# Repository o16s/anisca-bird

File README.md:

# Anisca Bird

## Overview

Anisca Bird is a smart weighing and tracking device developed by Octanis Instruments in collaboration with the Swiss Ornithological Institute. The system replaces a bird's regular roosting place with a weighing and tracking device that can register a bird's identity and body weight throughout the year without causing stress to the animal.

This repository contains the firmware, PCB design files, and mechanical designs to build and operate the Anisca Bird system.

## Key Features

- **RFID Identification**: Automatically reads passive RFID tags attached to birds
- **Weight Measurement**: Precision load cell with 1g resolution when calibrated
- **Data Storage**: Onboard memory for up to 18 years of weight records
- **Wireless Connectivity**: Optional Sigfox connectivity for remote data transmission
- **USB Connection**: Easy data transfer via USB-C port
- **Long Battery Life**: Up to 1 year with the external battery box
- **Modular Design**: Easy to modify, repair, or upgrade

## Repository Structure

- **`/mechanical`**: Mechanical design files (STEP format)
- **`/nestbox-electronics-master`**: PCB design files for the main board, RFID antenna, and battery box
  - **`/LF_Antenna_v3`**: RFID antenna PCB design
  - **`/Nestbox_v3_3*`**: Main board iterations
  - **`/battery_box`**: Battery box PCB design
  - **`/lib_fp.pretty`**: KiCad footprint libraries
  - **`/lib_sch`**: KiCad schematic libraries
- **`/nestbox-firmware-REV3.3`**: Firmware source code
  - **`/nestbox-fw`**: Core firmware files
  - **`/Core`**: Main application code
  - **`/Drivers`**: Hardware driver files
  - **`/Middlewares`**: Middleware components
  - **`/USB_DEVICE`**: USB communication stack

## Hardware Overview

The Anisca Bird system consists of three main components:

1. **Reader**: Contains the main PCB with microcontroller, load cell interface, RFID reader, flash memory, and connectivity options. Housed in a water-resistant aluminum case.

2. **Perch**: Varnished plywood perch with integrated 125kHz RFID antenna for tag reading with up to 10cm range.

3. **Battery Box**: External battery case with four 10Ah NiMH D-cells providing up to 1 year of operation.

## Firmware Overview

The firmware is built for STM32L433 microcontroller and provides the following functionality:

- RFID tag detection and decoding
- Weight measurement and analysis
- Low-power operation for extended battery life
- USB communication for data retrieval and configuration
- Optional Sigfox connectivity for remote data transmission

## License

Where not otherwise specified, the [GPL License](LICENSE) applies.

## Contact

For commercial support or to request an Anisca Bird system, please contact:

Octanis Instruments GmbH  
Europa-Strasse 33, 8152 Glattbrugg, Switzerland  
info@octanis.ch  
www.octanis.ch

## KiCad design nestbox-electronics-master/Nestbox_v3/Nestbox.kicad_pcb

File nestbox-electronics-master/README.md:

# Nestbox Electronics

All electronics design files and documentations are stored here.

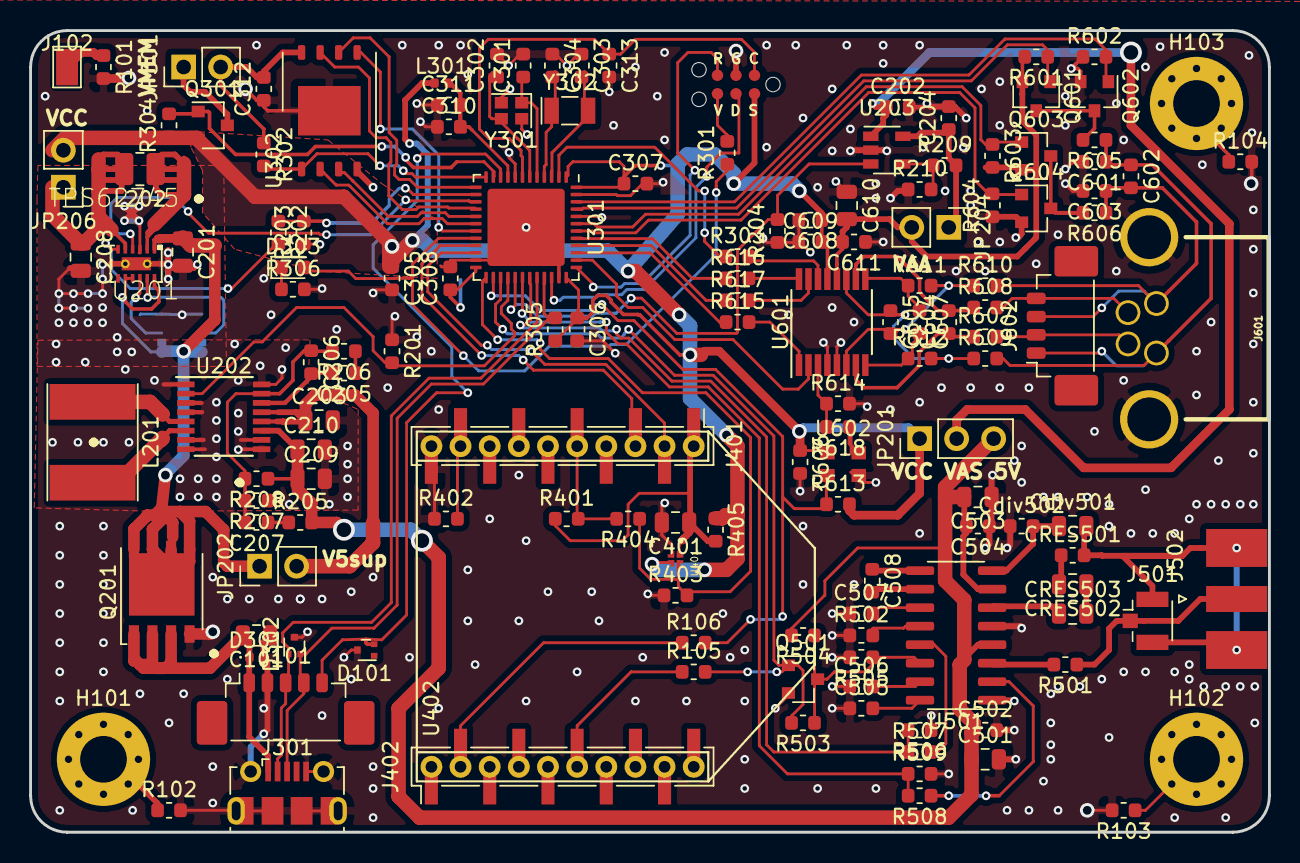
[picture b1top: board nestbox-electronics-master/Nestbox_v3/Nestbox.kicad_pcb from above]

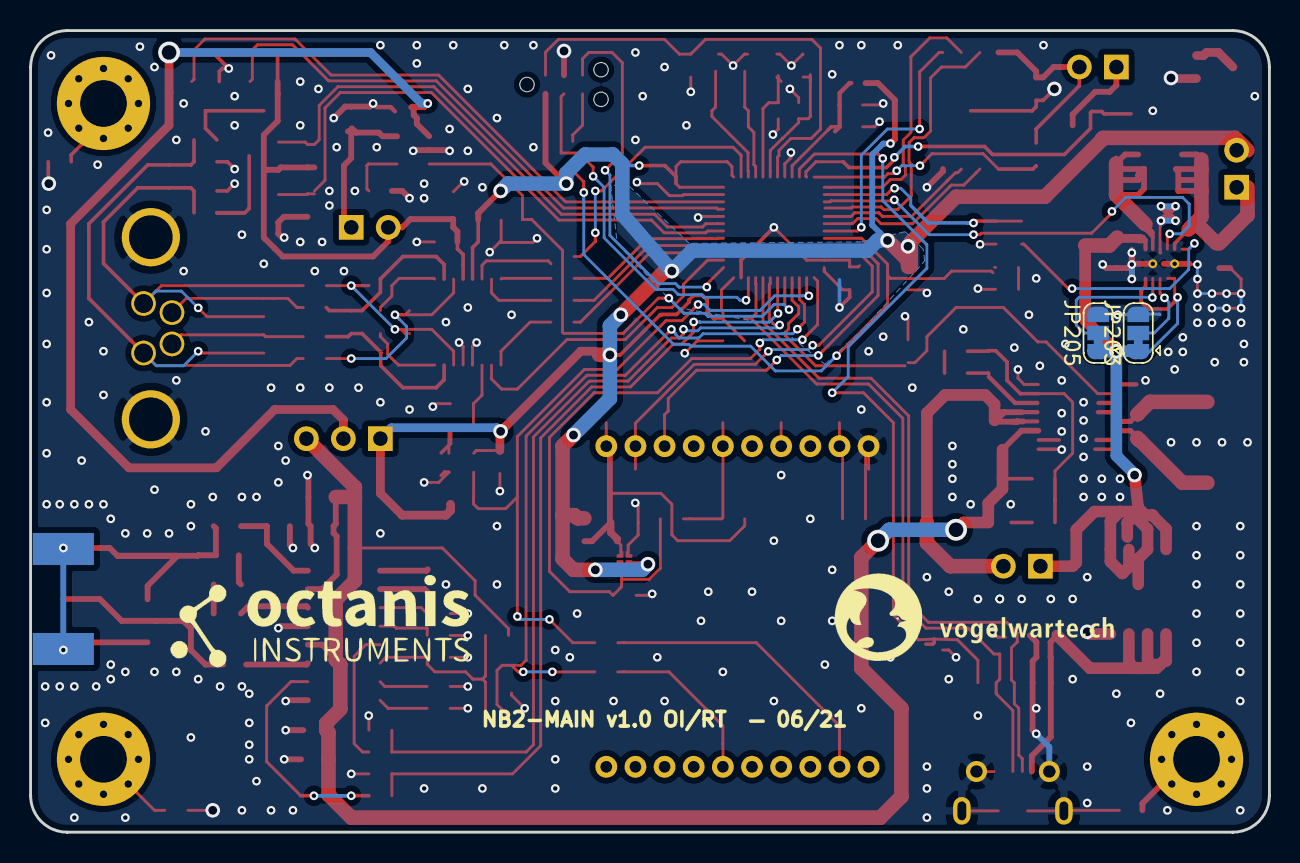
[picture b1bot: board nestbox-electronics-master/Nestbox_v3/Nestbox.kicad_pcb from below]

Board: 2 copper layers, 85.0 x 55.0 mm, 150 parts (4 on the bottom side), 108 nets.

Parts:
C101, C201, C203, C208, C209, C210, C401, C501, C503, C610: 10u; C_0805_2012Metric
C202, C311, C312, C608: 1u; C_0603_1608Metric
C204: 1u or 4u7 for adjustable version; C_0603_1608Metric
C205: 330p; C_0603_1608Metric
C206: 10p; C_0603_1608Metric
C207: 33p; C_0603_1608Metric
C301, C302: 12p; C_0603_1608Metric
C303, C304: 22p; C_0603_1608Metric
C305: 4u7; C_0603_1608Metric
C306, C307, C308, C313, C502, C504, C507, C606, C609: 100n; C_0603_1608Metric
C310, C505, C506, C611: 10n; C_0603_1608Metric
C508: DNP or 100n; C_0603_1608Metric
C601, C603, C604: 100n 1% DNP; C_0603_1608Metric
C602: 1u DNP; C_0603_1608Metric
C605, C607: 100n DNP; C_0603_1608Metric
CRES501: 0R; C_0603_1608Metric
CRES502, CRES503: 1n5 450V C0G; C_0805_2012Metric
Cdiv501: 10p 500V; C_0805_2012Metric
Cdiv502: 1n; C_0603_1608Metric
D101, D302: ESD7205; SOT-723
D301: TVS DIODE 12V 23.7V; D_0402_1005Metric
D303: LED_YELLOW; LED_0603_1608Metric
G101: LOGO; oi_logo_small
H101, H102, H103: MountingHole_Pad; MountingHole_3.2mm_M3_Pad_Via
J101: FC-M8-5; Molex_PicoBlade_53398-0571_1x05-1MP_P1.25mm_Vertical
J102: Chassis Pin; SMD_PAD
J301: USB_B_Micro; USB_Micro-B_Molex-105017-0001
J401, J402: Conn_01x10_Female; PinSocket_1x10_P2.00mm_Vertical_SMD_Pin1Left
J501: Conn_RFID_UFL_ALT; U.FL_Hirose_U.FL-R-SMT-1_Vertical
J502: Conn_RFID_SMA; SMA_Molex_EdgeMount
J601: LOAD_CELL_CONN_01X04; MB08MBSAFF04RA
J602: LOAD_CELL_CONN_01X04; Molex_PicoBlade_53398-0471_1x04-1MP_P1.25mm_Vertical
JP201: Jumper_3_Bridged12; PinHeader_1x03_P2.54mm_Vertical
JP202: 5V boost supply jumper; PinHeader_1x02_P2.54mm_Vertical
JP203: vsel 0.2; SolderJumper-3_P1.3mm_Bridged12_RoundedPad1.0x1.5mm
JP204: VAA jumper; PinHeader_1x02_P2.54mm_Vertical
JP205: vsel 0.1; SolderJumper-3_P1.3mm_Bridged12_RoundedPad1.0x1.5mm
JP206, JP301: Jumper_NC_Small; PinHeader_1x02_P2.54mm_Vertical
L201: 5uH; L_Taiyo-Yuden_NR-60xx_HandSoldering
L202: 4.7uH; L_1008_2520Metric
L301: 10u; L_0402_1005Metric
LOGO101: Logo_Open_Hardware_Small; VogelwarteLogo3
P301: TC2030-MCP; TC2030-MCP-NL
Q201: TPH1R712MDL1Q; TDSON-8-1_HandSoldering
Q301, Q601, Q603: DMG2301L-7; SOT-23
Q501, Q602, Q604: NMOS 30V 4A; SOT-23
R101, R102, R103, R104, R205, R401, R403: 10k; R_0603_1608Metric
R105, R106, R204, R209, R210, R301, R402, R404, R405, R503, R505, R506, R509, R613, R614: DNP; R_0603_1608Metric
R201, R202, R302, R304, R504, R601, R602, R603, R604: 82k; R_0603_1608Metric
R203: 47k; R_0603_1608Metric
R206: 15k; R_0603_1608Metric
R207: 162k 1%; R_0603_1608Metric
R208: 649k 1%; R_0603_1608Metric
R303: 100R; R_0603_1608Metric
R305: 1k5; R_0603_1608Metric
R306: 1k; R_0603_1608Metric
R501, R502, R507, R508, R605, R606, R607, R608, R609, R610, R611, R612, R618: 0R; R_0603_1608Metric
R615, R616, R617: 47R; R_0603_1608Metric
U201: TPS62745; WSON_3x2mm_12pin
U202: LTC3534; SSOP-16_3.9x4.9mm_P0.635mm
U203: 3.0V LDO; SOT-23-5
U301: STM32L433CCxx; QFN-48-1EP_7x7mm_P0.5mm_EP5.3x5.3mm
U302: 1Gb NAND Flash; 8-LGA-6x8mm
U401: Power Switch 2A, 800us soft start; IC_MIC94085YFT-TR
U402: XBEE
U501: EM4095; SOIC-16_3.9x9.9mm_P1.27mm
U601: ADS1220; TSSOP-16_4.4x5mm_P0.65mm
U602: SIT1602BI 4.096 MHz; Oscillator_SMD_EuroQuartz_XO32-4Pin_3.2x2.5mm
Y301: 16MHz 10ppm 9pF; Crystal_SMD_2016-4Pin_2.0x1.6mm
Y302: 32kHz 20ppm 12.5pF; Crystal_SMD_MicroCrystal_CC7V-T1A-2Pin_3.2x1.5mm

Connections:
+5V: C209.1, C210.1, C501.1, C502.1, C503.2, C504.2, JP201.3, R205.2, R208.1, R504.2, U202.11, U501.4, U501.7
+BATT: C201.1, JP202.1, JP203.1, JP205.1, Q201.3, U201.1, U201.8, U201.9, U201.12
/ADC_CLK_EN: R106.2, R613.1, U301.26, U602.1
/Communication/RF_CTS: J402.2, R106.1, U402.12
/Communication/RF_ENABLE: R403.2, R404.1, U301.25, U401.4
/Communication/RF_RTS: J402.6, R105.1, U402.16
/Communication/RF_RX: J401.3, U301.21, U402.3
/Communication/RF_TX: J401.2, U301.22, U402.2
/Communication/SUPER_B_EN: J401.5, R401.2, R404.2, U402.5
/Communication/SUPER_B_IO0: J401.7, U402.7
/Communication/dtr: J401.9, R402.2, U402.9
/Control/5V_ENABLE: R201.2, U202.2, U301.28
/Control/BAT_TEST_ENABLE: U201.4, U301.15
/Control/DBG_LED1: D303.2, R301.1, U301.20
/Control/FLASH_POWER_ON_N: Q301.1, R304.2, U301.11
/Control/HK_BAT_V: R202.1, R203.2, U301.14
/Control/LOADCELL_SPI_CS: U301.38, U601.2
/Control/QSPI_CSN: R302.2, U301.12, U302.1
/Control/QSPI_IO0: U301.19, U302.5
/Control/QSPI_IO1: U301.18, U302.2
/Control/QSPI_IO2: U301.17, U302.3
/Control/QSPI_IO3: U301.16, U302.7
/Control/QSPI_SCK: U301.13, U302.6
/Control/RFID_CLK: R506.2, R507.1, U301.31
/Control/RFID_DATA: R508.2, R509.1, U301.30
/Control/SPI_CLK: R615.1, U301.39
/Control/SPI_MISO: R617.1, U301.40
/Control/SPI_MOSI: R616.1, U301.41
/Load_Cell/ADC_CLK: R614.1, R618.2, U601.3
/Load_Cell/AIN1: C604.2, R608.1, U601.10
/Load_Cell/AIN2: C604.1, R607.1, U601.7
/Load_Cell/DRDY_N: R303.2, U601.14
/Load_Cell/EXC_A: C601.1, C602.1, J601.1, J602.1, R605.1, R609.2
/Load_Cell/EXC_A_N: Q602.1, R602.2, U301.46
/Load_Cell/EXC_A_P: Q601.1, R601.1, U301.45
/Load_Cell/EXC_B: C602.2, C603.1, J601.3, J602.3, R606.1, R610.2
/Load_Cell/EXC_B_N: Q604.1, R604.2, U301.42
/Load_Cell/EXC_B_P: Q603.1, R603.1, U301.43
/Load_Cell/green: J601.2, J602.2, R607.2
/Load_Cell/white: J601.4, J602.4, R608.2
/RFID/ant1: J501.1, J502.1, R501.1
/RFID/ant2: CRES501.2, Cdiv501.2, J501.2, J502.2
/RFID/demod_out: R507.2, U501.13
/RFID/rdyclk: R508.1, U501.2
/RFID/shd: Q501.3, R503.1, R504.1, R505.1, U501.14
/RFID_SLEEP_N: Q501.1, R105.2, R503.2, U301.27
/VAA_LDO_EN: R204.2, U203.3, U301.29
BAT_IN: C101.2, D301.1, J101.1, J301.1, Q201.1
GND: C101.1, C201.2, C202.2, C203.2, C204.2, C208.2, C209.2, C210.2, C301.2, C302.2, C303.1, C304.1, C305.2, C306.2, C307.2, C308.2, C310.1, C311.1, C312.1, C313.2, C401.2, C501.2, C502.2, C503.1, C504.1, C505.1, C506.1, C507.1, C601.2, C603.2, C606.2, C608.2, C609.1, C610.1, C611.1, Cdiv502.1, D101.3, D301.2, D302.3, J101.2, J301.5, J301.6, J401.10, J601.SH, JP203.3, JP205.3, P301.3, Q201.2, Q501.2, Q602.2, Q604.2, R101.2, R102.2, R103.2, R104.2, R201.1, R203.1, R204.1, R207.1, R210.1, R306.2, R402.1, R403.1, R502.1, R505.2, R506.1, R509.2, R602.1, R604.1, R614.2, U201.3, U201.GND1, U201.GND2, U202.1, U202.3, U202.4, U202.7, U202.8, U202.9, U202.10, U202.16, U203.2, U301.8, U301.23, U301.35, U301.44, U301.47, U301.49, U302.4, U302.9, U401.2, U402.10, U501.1, U501.5, U601.4, U601.5, U602.2, Y301.2, Y301.4
NRST: C313.1, P301.1, U301.7
unnamed: C202.1, JP201.2, U203.1
unnamed: C203.1, JP202.2, U202.12, U202.13
unnamed: C204.1, JP204.1, R209.2, U203.5
unnamed: C205.1, R206.1
unnamed: C205.2, C206.2, U202.14
unnamed: C206.1, C207.2, R206.2, R207.2, R208.2, U202.15
unnamed: C207.1, R205.1
unnamed: C208.1, JP206.1, L202.2, U201.5
unnamed: C301.1, U301.5, Y301.1
unnamed: C302.1, U301.6, Y301.3
unnamed: C303.2, U301.3, Y302.2
unnamed: C304.2, U301.4, Y302.1
unnamed: C310.2, C311.2, L301.2, U301.9
unnamed: C312.2, JP301.2, R302.1, U302.8
unnamed: C505.2, U501.16
unnamed: C506.2, U501.15
unnamed: C507.2, U501.11
unnamed: C508.1, U501.9
unnamed: C508.2, U501.10
unnamed: C605.1, R609.1, R612.2, U601.11
unnamed: C605.2, R610.1, R611.2, U601.6
unnamed: C607.1, R611.1, U601.9
unnamed: C607.2, R612.1, U601.8
unnamed: CRES501.1, CRES502.2
unnamed: CRES502.1, CRES503.2
unnamed: CRES503.1, U501.6
unnamed: Cdiv501.1, Cdiv502.2, U501.8
unnamed: D303.1, R306.1
unnamed: H101.1, R102.1
unnamed: H102.1, R103.1
unnamed: H103.1, R104.1
unnamed: J102.1, R101.1
unnamed: JP203.2, U201.10
unnamed: JP205.2, U201.11
unnamed: JP301.1, Q301.3
unnamed: L201.1, U202.5
unnamed: L201.2, U202.6
unnamed: L202.1, U201.2
unnamed: Q601.3, Q602.3, R605.2
unnamed: Q603.3, Q604.3, R606.2
unnamed: R202.2, U201.6
unnamed: R209.1, R210.2, U203.4
unnamed: R303.1, U301.2
unnamed: R501.2, U501.3
unnamed: R502.2, U501.12
unnamed: R615.2, U601.1
unnamed: R616.2, U601.16
unnamed: R617.2, U601.15
unnamed: R618.1, U602.3
RTC_OUT_CALIB: P301.6, R301.2
SWCLK: P301.5, U301.37
SWDIO: P301.4, U301.34
USB_D+: D302.2, J101.4, J301.3, R305.2, U301.33
USB_D-: D302.1, J101.3, J301.2, U301.32
USER_GPIO: D101.2, J101.5, U301.10
VAA: C610.2, C611.2, JP204.2, Q601.2, Q603.2, R601.2, R603.2, U601.12
VCC: C305.1, C306.1, C307.1, C308.1, C606.1, C608.1, C609.2, JP201.1, JP206.2, L301.1, P301.2, Q301.2, R304.1, R305.1, R405.1, R613.2, U301.1, U301.24, U301.36, U301.48, U401.3, U601.13, U602.4
VCOM: C401.1, J401.1, R401.1, R405.2, U401.1, U402.1

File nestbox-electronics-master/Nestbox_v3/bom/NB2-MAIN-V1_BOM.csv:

Reference, Quantity, Value, Footprint, Datasheet, MPN, MPN-adj, MPN2, Description, Height
C101 C201 C203 C208 C209 C210 C401 C501 C503 C610 ,10,"10u","Capacitor_SMD:C_0805_2012Metric",""
C202 C311 C312 C608 ,4,"1u","Capacitor_SMD:C_0603_1608Metric",""
C204 ,1,"1u or 4u7 for adjustable version","Capacitor_SMD:C_0603_1608Metric",""
C205 ,1,"330p","Capacitor_SMD:C_0603_1608Metric",""
C206 ,1,"10p","Capacitor_SMD:C_0603_1608Metric",""
C207 ,1,"33p","Capacitor_SMD:C_0603_1608Metric",""
C301 C302 ,2,"12p","Capacitor_SMD:C_0603_1608Metric","~"
C303 C304 ,2,"22p","Capacitor_SMD:C_0603_1608Metric","~"
C305 ,1,"4u7","Capacitor_SMD:C_0603_1608Metric","~"
C306 C307 C308 C313 C502 C504 C507 C606 C609 ,9,"100n","Capacitor_SMD:C_0603_1608Metric","~"
C310 C505 C506 C611 ,4,"10n","Capacitor_SMD:C_0603_1608Metric","~"
C508 ,1,"DNP or 100n","Capacitor_SMD:C_0603_1608Metric","DNP"
C602 ,1,"1u DNP","Capacitor_SMD:C_0603_1608Metric",""
C601 C603 C604 ,3,"100n 1% DNP","Capacitor_SMD:C_0603_1608Metric",""
C605 C607 ,2,"100n DNP","Capacitor_SMD:C_0603_1608Metric",""
CRES501 ,1,"0R","Capacitor_SMD:C_0603_1608Metric",""
CRES502 CRES503 ,2,"1n5 450V C0G","Capacitor_SMD:C_0805_2012Metric","","CGA4F4C0G2W152J085AE","","","",""
Cdiv501 ,1,"10p 500V","Capacitor_SMD:C_0805_2012Metric","","C0805C100JDGACTU","","","",""
Cdiv502 ,1,"1n","Capacitor_SMD:C_0603_1608Metric",""
D101 D302 ,2,"ESD7205","Package_TO_SOT_SMD:SOT-723","","SZESD7205DT5G","","","",""
D301 ,1,"TVS DIODE 12V 23.7V","Diode_SMD:D_0402_1005Metric","~","ESD9X12ST5G","","","",""
D303 ,1,"LED_YELLOW","LED_SMD:LED_0603_1608Metric",""
G101 ,1,"LOGO","lib-fp-global:oi_logo_small",""
H101 H102 H103 ,3,"MountingHole_Pad","MountingHole:MountingHole_3.2mm_M3_Pad_Via","~"
J101 ,1,"FC-M8-5","Connector_Molex:Molex_PicoBlade_53398-0571_1x05-1MP_P1.25mm_Vertical","http://www.mouser.com/ds/2/18/40_c091_abd_e-75918.pdf","53398-0571","","","",""
J102 ,1,"Chassis Pin","lib_fp:SMD_PAD","~"
J301 ,1,"USB_B_Micro","Connector_USB:USB_Micro-B_Molex-105017-0001","~"
J401 J402 ,2,"Conn_01x10_Female","Connector_PinSocket_2.00mm:PinSocket_1x10_P2.00mm_Vertical_SMD_Pin1Left","~","1-2307813-0","","","",""
J501 ,1,"Conn_RFID_UFL_ALT","Connector_Coaxial:U.FL_Hirose_U.FL-R-SMT-1_Vertical"," ~","U.FL-R-SMT(10)","","","",""
J502 ,1,"Conn_RFID_SMA","lib_fp:SMA_Molex_EdgeMount"," ~","0732512120","","","",""
J601 ,1,"LOAD_CELL_CONN_01X04","lib_fp:MB08MBSAFF04RA","","M8S-04PMMR-SF8001","","MB08MBSAFF04RA","",""
J602 ,1,"LOAD_CELL_CONN_01X04","Connector_Molex:Molex_PicoBlade_53398-0471_1x04-1MP_P1.25mm_Vertical","","53398-0471","","","",""
JP201 ,1,"Jumper_3_Bridged12","Connector_PinHeader_2.54mm:PinHeader_1x03_P2.54mm_Vertical","~"
JP202 ,1,"5V boost supply jumper","Connector_PinHeader_2.54mm:PinHeader_1x02_P2.54mm_Vertical","~"
JP203 ,1,"vsel 0.2","Jumper:SolderJumper-3_P1.3mm_Bridged12_RoundedPad1.0x1.5mm","~"
JP204 ,1,"VAA jumper","Connector_PinHeader_2.54mm:PinHeader_1x02_P2.54mm_Vertical","~"
JP205 ,1,"vsel 0.1","Jumper:SolderJumper-3_P1.3mm_Bridged12_RoundedPad1.0x1.5mm","~"
JP206 JP301 ,2,"Jumper_NC_Small","Connector_PinHeader_2.54mm:PinHeader_1x02_P2.54mm_Vertical","~"
L201 ,1,"5uH","Inductor_SMD:L_Taiyo-Yuden_NR-60xx_HandSoldering","","MSS7341-502NLD","","","",""
L202 ,1,"4.7uH","Inductor_SMD:L_1008_2520Metric","","DFE252010P-4R7M=P2","","","",""
L301 ,1,"10u","Inductor_SMD:L_0402_1005Metric","~","MPZ1005S300CT000","","","",""
LOGO101 ,1,"Logo_Open_Hardware_Small","lib_fp:VogelwarteLogo3","~"
P301 ,1,"TC2030-MCP","lib-fp-global:TC2030-MCP-NL",""
Q201 ,1,"TPH1R712MDL1Q","lib_fp:TDSON-8-1_HandSoldering","","TPH1R712MD,L1Q","","","",""
Q301 Q601 Q603 ,3,"DMG2301L-7","Package_TO_SOT_SMD:SOT-23","","DMG2301L-7","","","",""
Q501 Q602 Q604 ,3,"NMOS 30V 4A","Package_TO_SOT_SMD:SOT-23","","SI2316DS-T1-E3","","","",""
R101 R102 R103 R104 R205 R401 R403 ,7,"10k","Resistor_SMD:R_0603_1608Metric","~"
R105 R106 R204 R209 R210 R301 R402 R404 R405 R503 R505 R506 R509 R613 R614 ,15,"DNP","Resistor_SMD:R_0603_1608Metric","~"
R201 R202 R302 R304 R504 R601 R602 R603 R604 ,9,"82k","Resistor_SMD:R_0603_1608Metric",""
R203 ,1,"47k","Resistor_SMD:R_0603_1608Metric",""
R206 ,1,"15k","Resistor_SMD:R_0603_1608Metric",""
R207 ,1,"162k 1%","Resistor_SMD:R_0603_1608Metric","","RC0402FR-07162KL","","","",""
R208 ,1,"649k 1%","Resistor_SMD:R_0603_1608Metric","","RC0402FR-07649KL","","","",""
R303 ,1,"100R","Resistor_SMD:R_0603_1608Metric","~"
R305 ,1,"1k5","Resistor_SMD:R_0603_1608Metric","~"
R306 ,1,"1k","Resistor_SMD:R_0603_1608Metric",""
R501 R502 R507 R508 R605 R606 R607 R608 R609 R610 R611 R612 R618 ,13,"0R","Resistor_SMD:R_0603_1608Metric",""
R615 R616 R617 ,3,"47R","Resistor_SMD:R_0603_1608Metric",""
U201 ,1,"TPS62745","lib_fp:WSON_3x2mm_12pin","","TPS62745DSSR","","","",""
U202 ,1,"LTC3534","Package_SO:SSOP-16_3.9x4.9mm_P0.635mm","","LTC3534EDHC#PBF","","","",""
U203 ,1,"3.0V LDO ","Package_TO_SOT_SMD:SOT-23-5","","TPS70630DBVR","TPS76201QDBVRQ1 ","TPS7A20","",""
U301 ,1,"STM32L433CCxx","Package_DFN_QFN:QFN-48-1EP_7x7mm_P0.5mm_EP5.3x5.3mm","http://www.st.com/st-web-ui/static/active/en/resource/techni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","STM32L433CCU6","","","",""
U302 ,1,"1Gb NAND Flash","lib_fp:8-LGA-6x8mm","","GD5F1GQ4UFYIGR","","","",""
U401 ,1,"Power Switch 2A, 800us soft start","lib_fp:IC_MIC94085YFT-TR","","MIC94082YFT-TR","","","",""
U402 ,1,"XBEE","lib_fp:XBEE","","SuperBx","","","",""
U501 ,1,"EM4095","Package_SO:SOIC-16_3.9x9.9mm_P1.27mm","","EM4095","","","",""
U601 ,1,"ADS1220","Package_SO:TSSOP-16_4.4x5mm_P0.65mm","","ADS1220IPW","","","",""
U602 ,1,"SIT1602BI 4.096 MHz","Oscillator:Oscillator_SMD_EuroQuartz_XO32-4Pin_3.2x2.5mm","https://abracon.com/Oscillators/ASDMB.pdf","SIT1602BI-21-XXE-4.096000","","","",""
Y301 ,1,"16MHz 10ppm 9pF","lib_fp:Crystal_SMD_2016-4Pin_2.0x1.6mm","","ECS-160-9-37-CKM-TR","",""," 16MHz ±10ppm Crystal 9pF 100 Ohms 4-SMD, No Lead ","0.6"
Y302 ,1,"32kHz 20ppm 12.5pF","lib_fp:Crystal_SMD_MicroCrystal_CC7V-T1A-2Pin_3.2x1.5mm","~","CM7V-T1A-32.768kHz-12.5pF-20PPM-TB-QC","","","",""

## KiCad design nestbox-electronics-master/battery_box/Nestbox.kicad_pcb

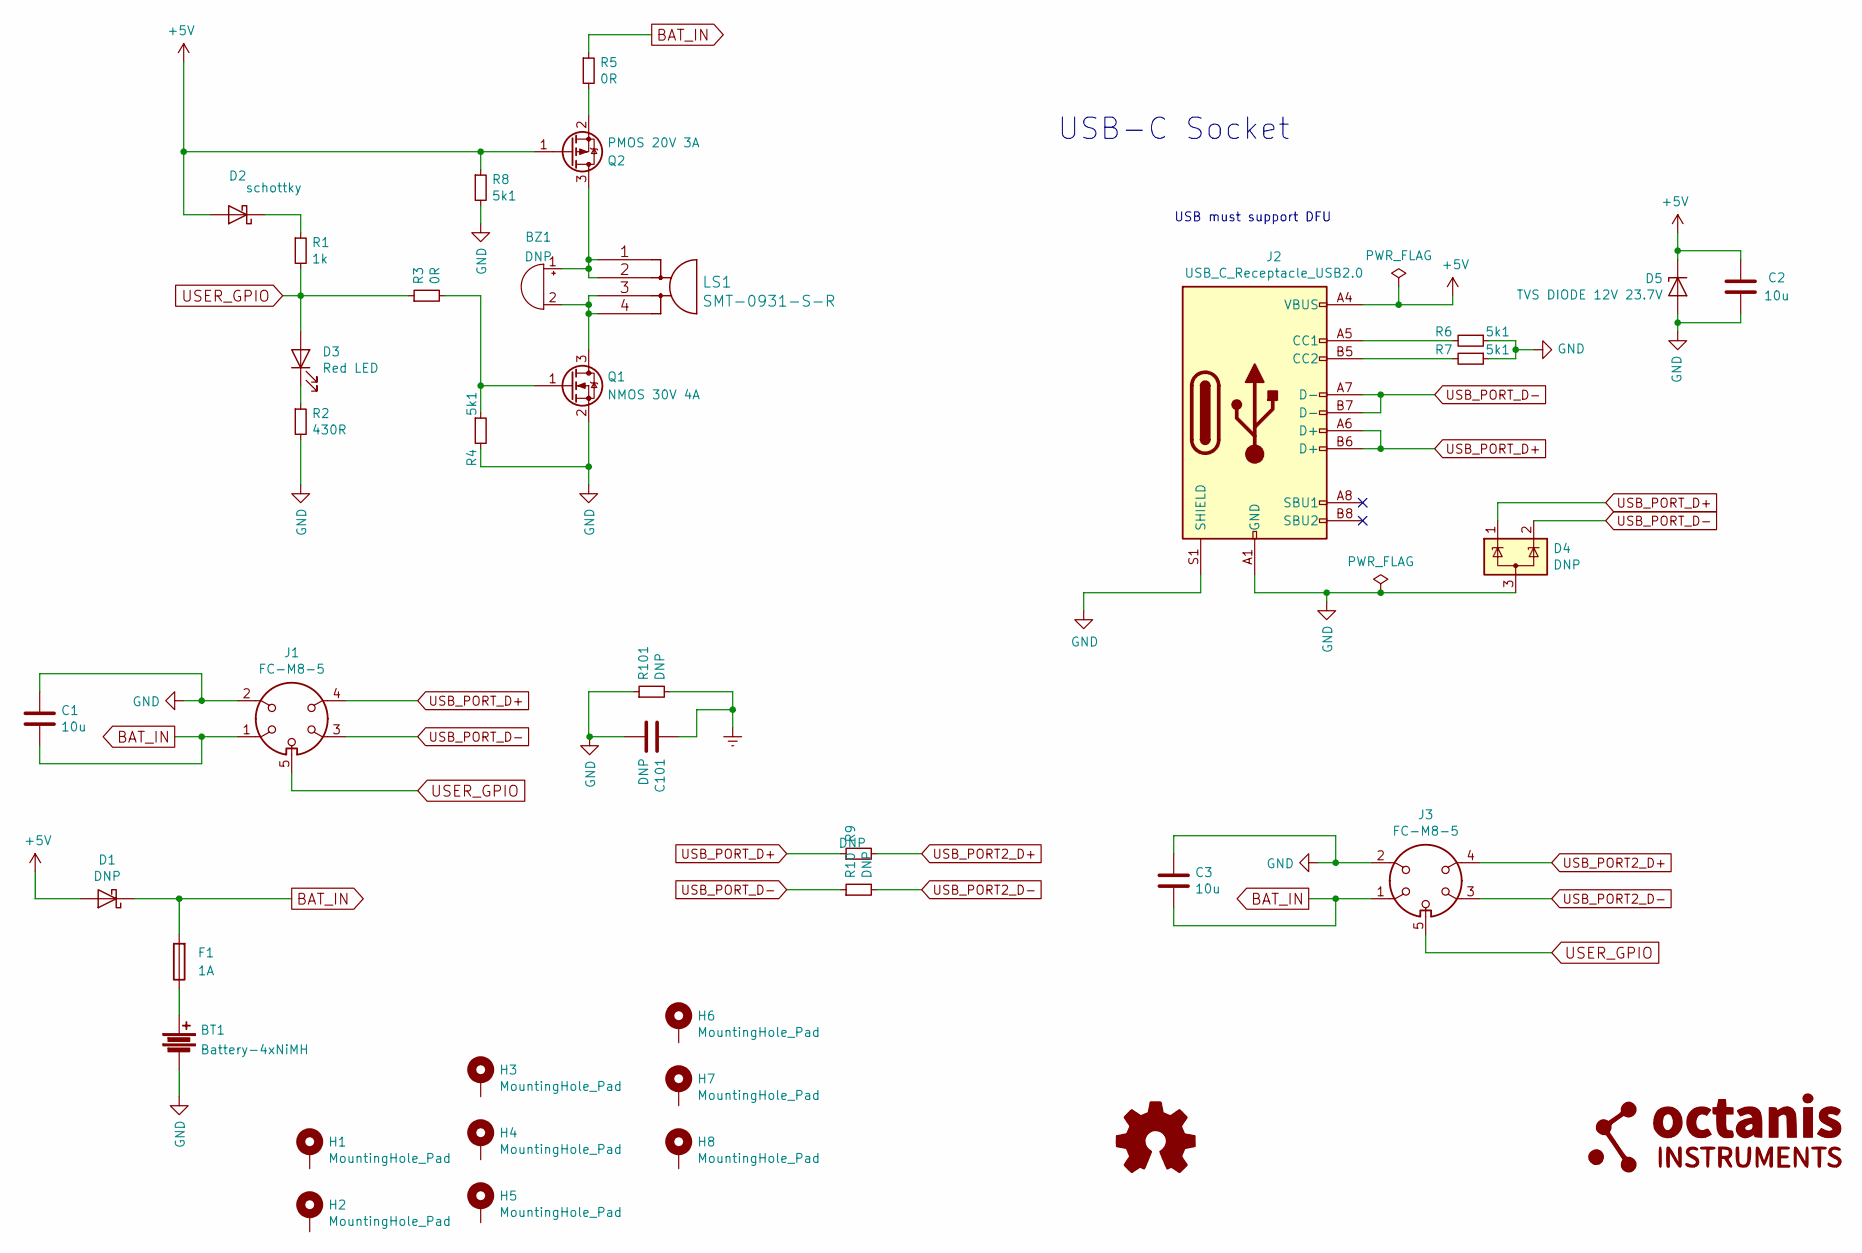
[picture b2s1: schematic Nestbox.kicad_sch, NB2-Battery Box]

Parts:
BT1: Battery-4xNiMH; TerminalBlock_Dinkle_DT-55-B01X-02_P10.00mm
BZ1: DNP; Buzzer_CUI_CPT-9019S-SMT; MPN SMT-0827-SW-5V-R
C1, C2, C3: 10u; C_0805_2012Metric
C101: DNP; C_0805_2012Metric
D1: DNP; D_SOD-323; MPN B0520WS-7-F
D2: schottky; D_SOD-323; MPN B0520WS-7-F
D3: Red LED; LED_D5.0mm; MPN WP934EW/ID
D4: DNP; SOT-723; MPN SZESD7205DT5G
D5: TVS DIODE 12V 23.7V; D_SOD-523; MPN UCLAMP1201H.TCT
F1: 1A; 0154001.DR; MPN 0154001.DR
G1: LOGO; oi_logo_small
H1, H3, H5, H7: MountingHole_Pad; MountingHole_4.5mm
H2, H4, H6, H8: MountingHole_Pad; MountingHole_3.5mm
J1, J3: FC-M8-5; M8-5pin_2.9mm_hole; MPN2 1424240
J2: USB_C_Receptacle_USB2.0; USB_C_Receptacle_HRO_TYPE-C-31-M-12; MPN USB4105-GF-A
LOGO1: Logo_Open_Hardware_Small; VogelwarteLogo3
LS1: SMT-0931-S-R; MPN SMT-0931-S-R
Q1: NMOS 30V 4A; SOT-23; MPN PMV45EN2R
Q2: PMOS 20V 3A; SOT-23; MPN DMP2160U-7
R1: 1k; R_0603_1608Metric
R2: 430R; R_0603_1608Metric
R3, R5: 0R; R_0603_1608Metric
R4, R6, R7, R8: 5k1; R_0603_1608Metric
R9, R10, R101: DNP; R_0603_1608Metric

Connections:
+5V: C2.1, D1.2 (A), D2.2 (A), D5.1 (K), J2.A4 (VBUS), J2.A9 (VBUS), J2.B4 (VBUS), J2.B9 (VBUS), Q2.1 (G), R8.1
BAT_IN: C1.2, C3.2, D1.1 (K), F1.2, J1.1, J3.1, R5.1
Earth: C101.1, R101.2
GND: BT1.2, C1.1, C2.2, C3.1, C101.2, D4.3 (A), D5.2 (A), J1.2, J2.A1 (GND), J2.A12 (GND), J2.B1 (GND), J2.B12 (GND), J2.S1 (SHIELD), J3.2, Q1.2 (S), R2.2, R4.2, R6.1, R7.1, R8.2, R101.1
unnamed: BT1.1, F1.1
unnamed: BZ1.1 (-), LS1.1, LS1.2, Q2.3 (D)
unnamed: BZ1.2 (+), LS1.3, LS1.4, Q1.3 (D)
unnamed: D2.1 (K), R1.1
unnamed: D3.1 (K), R2.1
unnamed: J2.A5 (CC1), R6.2
unnamed: J2.B5 (CC2), R7.2
unnamed: Q1.1 (G), R3.2, R4.1
unnamed: Q2.2 (S), R5.2
USB_PORT2_D+: J3.4, R9.2
USB_PORT2_D-: J3.3, R10.2
USB_PORT_D+: D4.1 (K), J1.4, J2.A6 (D+), J2.B6 (D+), R9.1
USB_PORT_D-: D4.2 (K), J1.3, J2.A7 (D-), J2.B7 (D-), R10.1
USER_GPIO: D3.2 (A), J1.5, J3.5, R1.2, R3.1

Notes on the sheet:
USB-C Socket
USB must support DFU

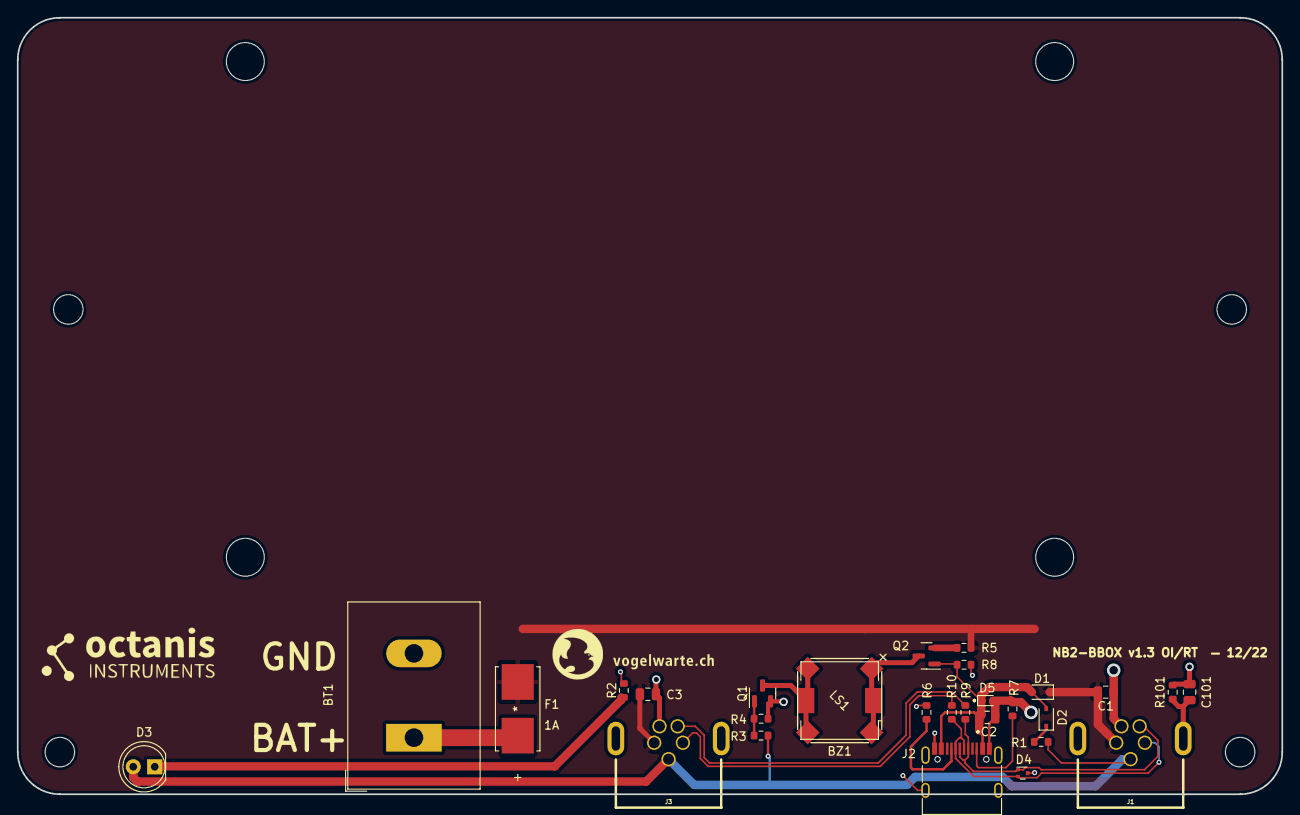
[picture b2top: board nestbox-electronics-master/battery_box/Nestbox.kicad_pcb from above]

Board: 2 copper layers, 150.0 x 92.1 mm, 39 parts (0 on the bottom side), 18 nets.

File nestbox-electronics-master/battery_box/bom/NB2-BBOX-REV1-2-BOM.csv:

Reference, Quantity, Value, Footprint, Datasheet, MPN, MPN2
BT1 ,1,"Battery-4xNiMH","TerminalBlock_Dinkle:TerminalBlock_Dinkle_DT-55-B01X-02_P10.00mm",""
BZ1 ,1,"DNP","Buzzer_Beeper:Buzzer_CUI_CPT-9019S-SMT","","SMT-0827-SW-5V-R",""
C1 C2 C3 ,3,"10u","Capacitor_SMD:C_0805_2012Metric",""
C101 ,1,"DNP","Capacitor_SMD:C_0805_2012Metric",""
D1 ,1,"DNP","Diode_SMD:D_SOD-323","","B0520WS-7-F",""
D2 ,1,"schottky","Diode_SMD:D_SOD-323","","B0520WS-7-F",""
D3 ,1,"Red LED","LED_THT:LED_D5.0mm","","WP934EW/ID",""
D4 ,1,"DNP","Package_TO_SOT_SMD:SOT-723","","SZESD7205DT5G",""
D5 ,1,"TVS DIODE 12V 23.7V","Diode_SMD:D_SOD-523","","UCLAMP1201H.TCT",""
G1 ,1,"LOGO","lib_fp_global:oi_logo_small",""
H1 H3 H5 H7 ,4,"MountingHole_Pad","MountingHole:MountingHole_4.5mm",""
H2 H4 H6 H8 ,4,"MountingHole_Pad","MountingHole:MountingHole_3.5mm",""
J1 J3 ,2,"FC-M8-5","lib_fp:M8-5","http://www.mouser.com/ds/2/18/40_c091_abd_e-75918.pdf","MB08MBSBFF05RA","1424240"
J2 ,1,"USB_C_Receptacle_USB2.0","lib_fp:USB_C_Receptacle_HRO_TYPE-C-31-M-12","https://www.jae.com/en/releases/detail/id=92529","USB4105-GF-A",""
LOGO1 ,1,"Logo_Open_Hardware_Small","lib_fp:VogelwarteLogo3",""
LS1 ,1,"SMT-0931-S-R","lib_fp:SMT-0931-S-R","","SMT-0931-S-R",""
Q1 ,1,"NMOS 30V 4A","Package_TO_SOT_SMD:SOT-23","","PMV45EN2R",""
Q2 ,1,"PMOS 20V 3A","Package_TO_SOT_SMD:SOT-23","","DMP2160U-7",""
R1 ,1,"1k","Resistor_SMD:R_0603_1608Metric",""
R2 ,1,"430R","Resistor_SMD:R_0603_1608Metric",""
R3 R5 ,2,"0R","Resistor_SMD:R_0603_1608Metric",""
R4 R6 R7 R8 ,4,"5k1","Resistor_SMD:R_0603_1608Metric",""
R10 R101 R9 ,3,"DNP","Resistor_SMD:R_0603_1608Metric",""

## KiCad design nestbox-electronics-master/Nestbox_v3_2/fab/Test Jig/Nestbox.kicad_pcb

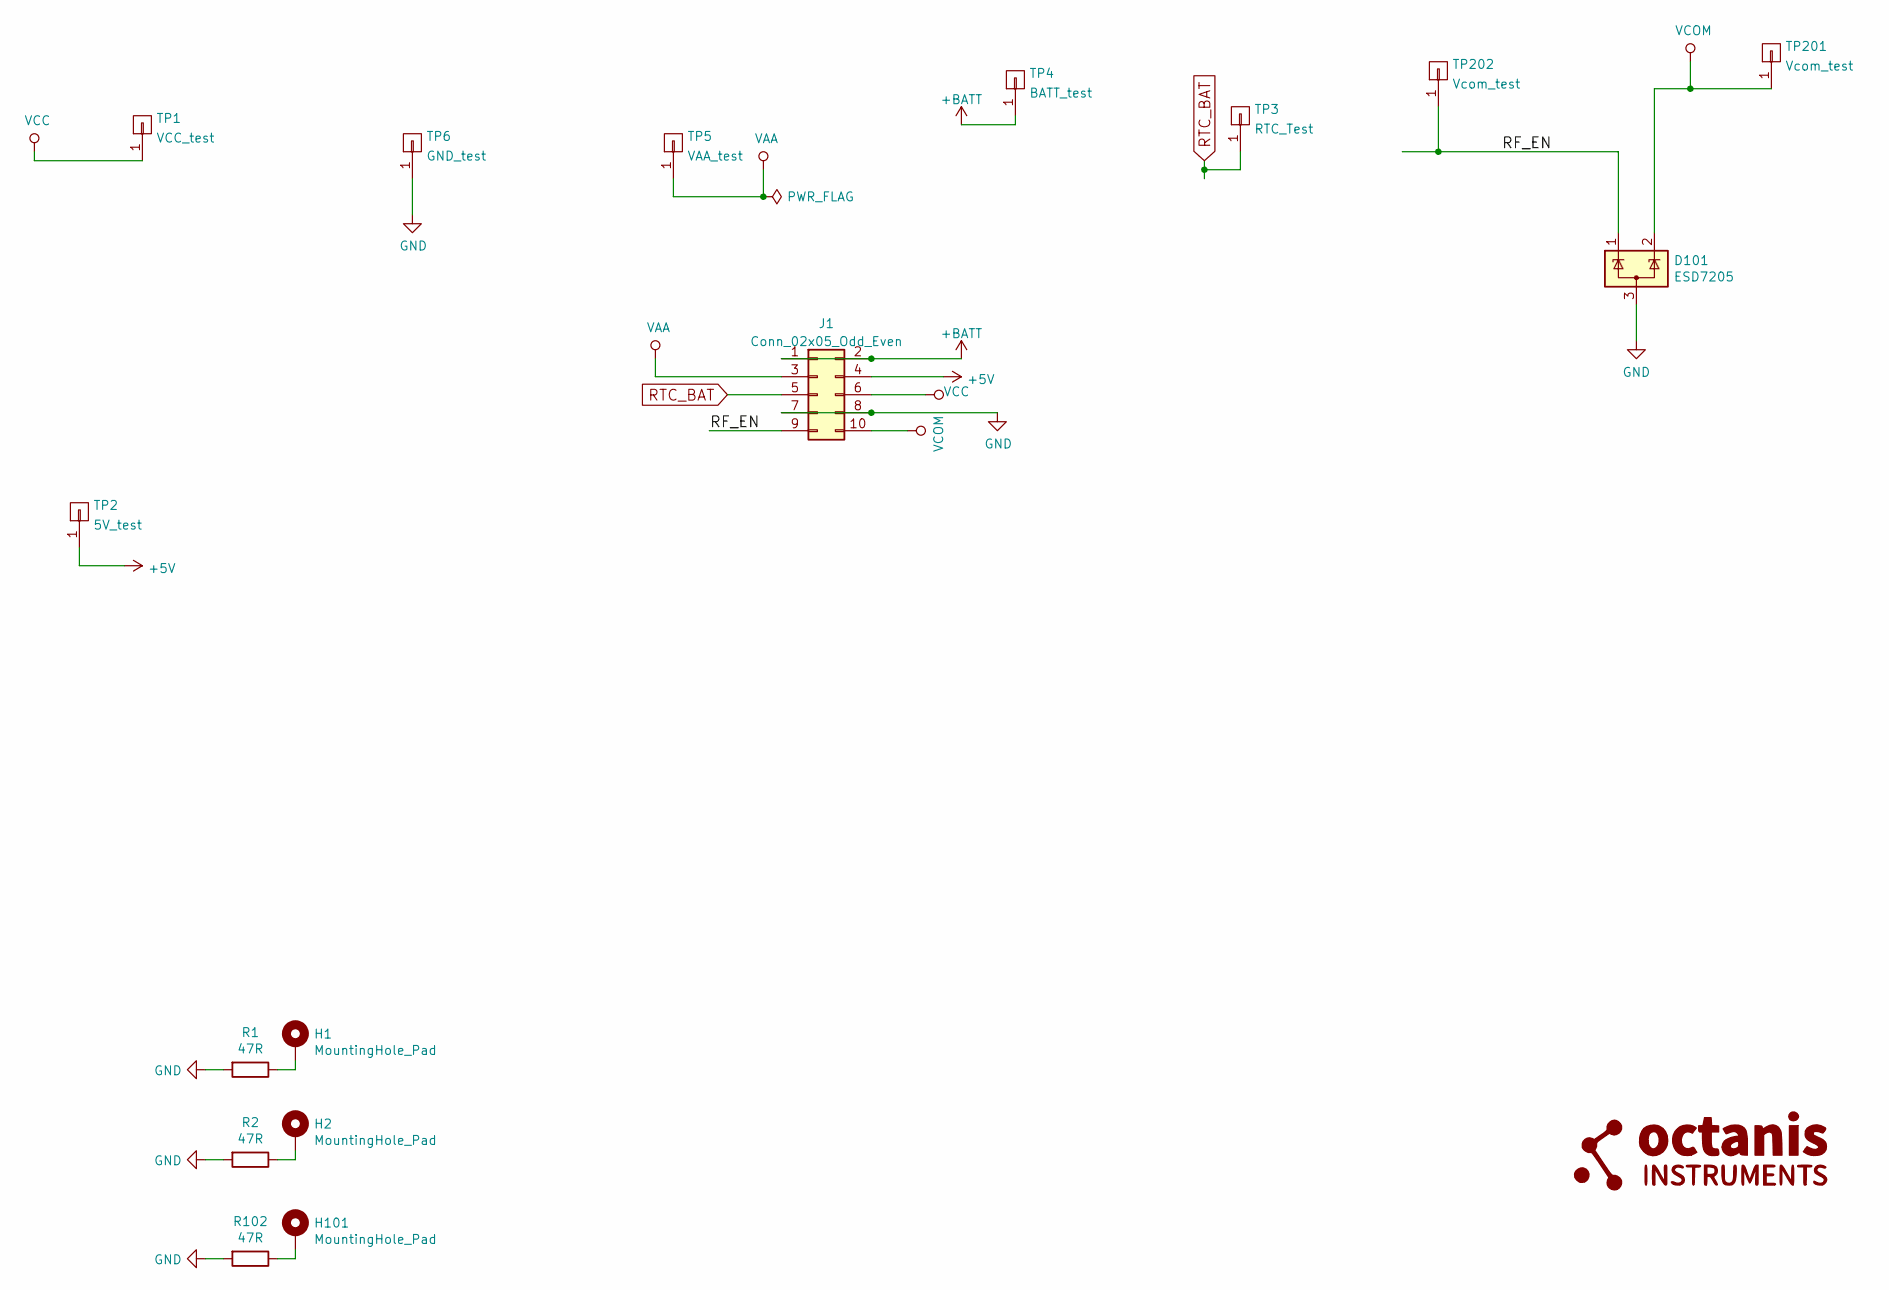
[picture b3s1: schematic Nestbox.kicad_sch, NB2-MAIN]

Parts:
D101: ESD7205; SOT-723; MPN SZESD7205DT5G
G101: LOGO; oi_logo_small
H1, H2, H101: MountingHole_Pad; MountingHole_2.5mm_Pad
J1: Conn_02x05_Odd_Even; IDC-Header_2x05_P2.54mm_Horizontal
R1, R2, R102: 47R; R_0603_1608Metric
TP1: VCC_test; Pin_D0.7mm_L6.5mm_W1.8mm_FlatFork
TP2: 5V_test; Pin_D0.7mm_L6.5mm_W1.8mm_FlatFork
TP3: RTC_Test; Pin_D0.7mm_L6.5mm_W1.8mm_FlatFork
TP4: BATT_test; Pin_D0.7mm_L6.5mm_W1.8mm_FlatFork
TP5: VAA_test; Pin_D0.7mm_L6.5mm_W1.8mm_FlatFork
TP6: GND_test; Pin_D0.7mm_L6.5mm_W1.8mm_FlatFork
TP201, TP202: Vcom_test; Pin_D0.7mm_L6.5mm_W1.8mm_FlatFork

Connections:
+5V: J1.4, TP2.1
+BATT: J1.1, J1.2, TP4.1
/RF_EN: D101.1 (K), J1.9, TP202.1
GND: D101.3 (A), J1.7, J1.8, R1.2, R2.2, R102.2, TP6.1
unnamed: H1.1, R1.1
unnamed: H2.1, R2.1
unnamed: H101.1, R102.1
RTC_BAT: J1.5, TP3.1
VAA: J1.3, TP5.1
VCC: J1.6, TP1.1
VCOM: D101.2 (K), J1.10, TP201.1

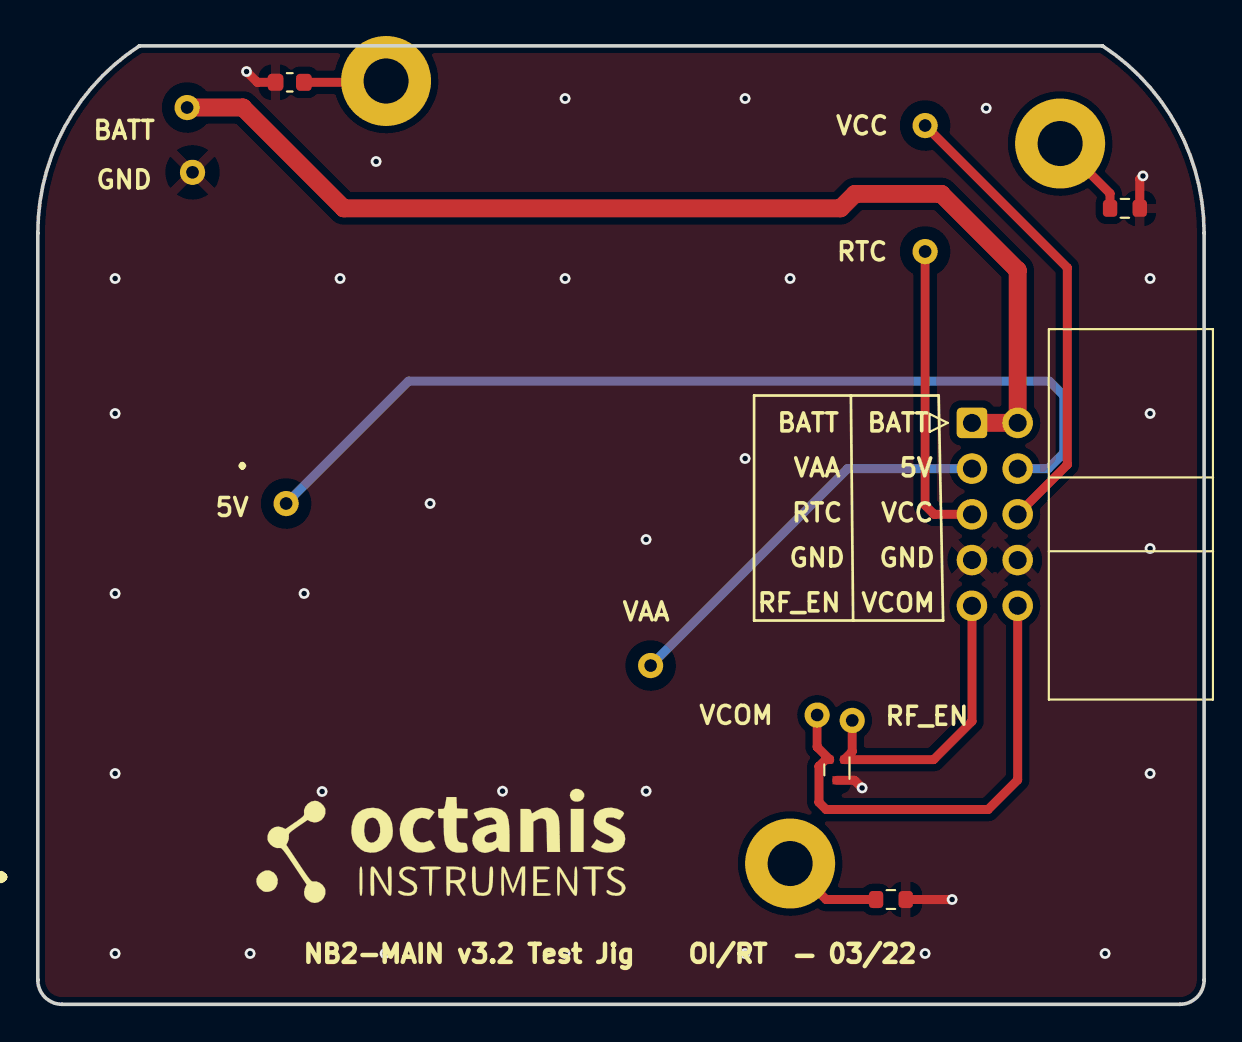
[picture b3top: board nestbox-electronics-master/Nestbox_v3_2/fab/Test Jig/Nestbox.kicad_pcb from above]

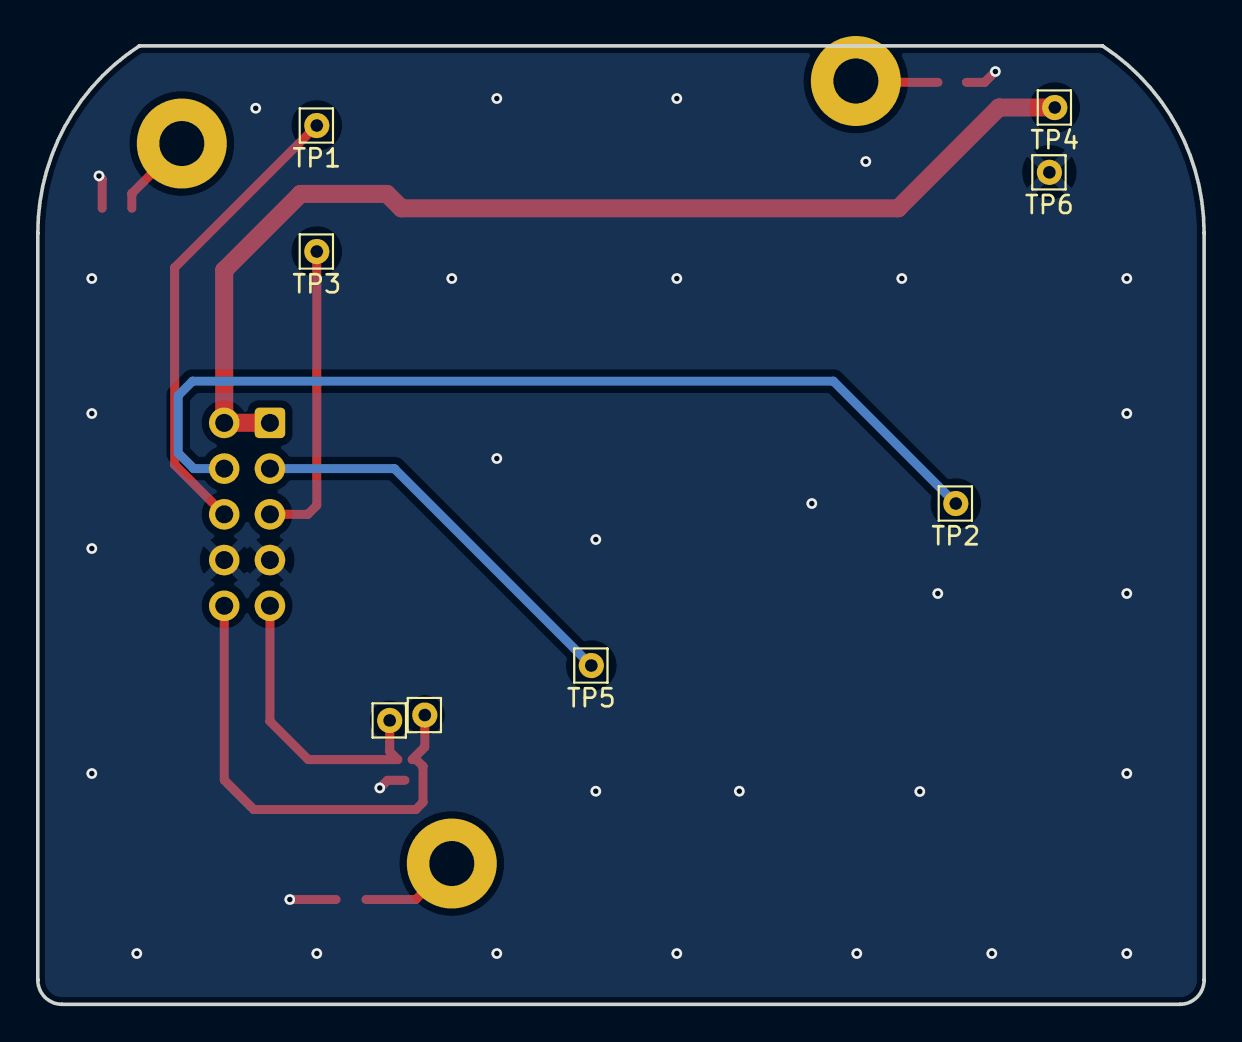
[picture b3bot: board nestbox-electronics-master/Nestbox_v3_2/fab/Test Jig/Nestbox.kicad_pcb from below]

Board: 2 copper layers, 64.8 x 53.2 mm, 17 parts (8 on the bottom side), 11 nets.

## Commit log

2022-03-30 adding webhook docs
2022-03-30 adding requirements
2022-03-30 updating format
2022-05-04 updating docs
2022-05-04 formatting fix
2022-05-14 adding info about the uid
2023-02-13 added documentation for weight acquisition
2025-05-21 adding fw, pcb, mech

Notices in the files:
parts and their libraries:
Copyright 2021 Accelerated Designs. All rights reserved.
